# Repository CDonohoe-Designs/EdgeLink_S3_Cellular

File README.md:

# EdgeLink S3 Cellular

**ESP32-S3 Embedded Hardware Design | LTE-M / NB-IoT | GNSS | Battery Power Management | Four-Layer PCB | KiCad**

## Engineering overview

EdgeLink S3 Cellular is a four-layer embedded hardware platform combining an ESP32-S3 controller, SIM7080G cellular/GNSS modem, USB-C, battery power management and environmental/motion sensing.

I developed the Rev A schematic and PCB as an engineering portfolio project, demonstrating system architecture, wireless module integration, power-tree design, digital interfaces, multilayer layout and manufacturing documentation.

**Project status:** The schematic, PCB and manufacturing package are complete as design deliverables. Rev A is an **unbuilt design**; hardware bring-up and physical performance testing have not been completed.

## Engineering portfolio — start here

| Resource | Contents |
| --- | --- |
| **[Illustrated engineering portfolio (PDF)](docs/portfolio/EdgeLink_S3_Cellular/EdgeLink_S3_Cellular_Engineering_Portfolio.pdf)** | Six-page visual case study with genuine PCB renders, schematic extracts and manufacturing evidence |
| [Editable portfolio (Word)](docs/portfolio/EdgeLink_S3_Cellular/EdgeLink_S3_Cellular_Engineering_Portfolio.docx) | Editable report |
| [Portfolio images](docs/portfolio/EdgeLink_S3_Cellular/images/) | PCB top/bottom views, four copper layers, circuit extracts and CAD renders |
| [System architecture](docs/images/architecture-reva.svg) | Functional system diagram |
| [Complete schematic PDF](docs/schematics/EdgeLink_S3_Cellular_RevA_Schematic.pdf) | Hierarchical schematic |
| [Editable KiCad project](hardware/kicad/EdgeLink_S3_Cellular_RevA/EdgeLink_S3_Cellular.kicad_pro) | PCB, schematic and supporting libraries |
| [Manufacturing package](manufacturing/REV_A/) | Gerbers, BOM and component placement |

## Hardware architecture

| Subsystem | Implementation |
| --- | --- |
| Controller | ESP32-S3-MINI-1-N8 with Wi-Fi/Bluetooth LE and native USB |
| Cellular and positioning | SIMCom SIM7080G LTE-M / NB-IoT and GNSS |
| Charging and power path | TI BQ25185 |
| 3.3 V regulation | TI TPS63802 buck-boost |
| Battery monitoring | MAX17048 fuel gauge |
| Motion sensing | Bosch BMI323 six-axis IMU |
| Environmental sensing | SHT40 temperature/humidity and BMP384 pressure |
| External interfaces | USB-C, Nano-SIM, LTE/GNSS U.FL, battery and I²C |

USB-C provides input power and native USB data. The BQ25185 manages the battery and system supply, while the TPS63802 generates the main 3.3 V rail. The cellular modem is powered from the battery supply through its input filtering. The sensor subsystem uses I²C connections to the ESP32-S3.

## Schematic engineering

The hierarchical schematic separates power and USB, ESP32-S3 processing, cellular/GNSS and sensor interfaces. Key circuits include battery charging and regulation, modem power and UART connectivity, RF antenna interfaces, USB-C protection and digital sensor integration.

### ESP32-S3 controller core

The ESP32-S3-MINI-1-N8 schematic brings together the controller supply and decoupling, native USB connections, modem control signals, I²C interfaces, reset/boot circuitry and status LED.

### USB-C interface

## Four-layer PCB implementation

The Rev A PCB integrates power conversion, digital processing, wireless communications and sensors on a nominal 56 × 52 mm board. The layout uses four copper layers with local component decoupling and functional grouping of power, RF and digital circuitry.

Additional PCB views and genuine KiCad CAD renders are included in the [illustrated portfolio](docs/portfolio/EdgeLink_S3_Cellular/EdgeLink_S3_Cellular_Engineering_Portfolio.pdf).

## Manufacturing documentation

The Rev A package includes fabrication Gerbers, drill files, a supplier-oriented BOM with LCSC references and component placement data for JLCPCB-oriented assembly preparation.

The assembly BOM contains 46 component groups covering 89 fitted references, matched by the component placement list.

## Engineering capabilities demonstrated

- ESP32-S3 and wireless modem hardware integration
- USB-C and digital peripheral interfaces
- Battery charging, power-path and buck-boost architecture
- Four-layer PCB design and RF-aware placement/routing
- Hierarchical KiCad schematic capture and component libraries
- Supplier-oriented BOM, CPL and Gerber preparation
- Technical documentation and traceable engineering deliverables

## Repository guide

| Location | Contents |
| --- | --- |
| [Portfolio](docs/portfolio/EdgeLink_S3_Cellular/) | Illustrated PDF, Word report and supporting images |
| [KiCad source](hardware/kicad/EdgeLink_S3_Cellular_RevA/) | Editable design and local assets |
| [Architecture notes](docs/architecture/README.md) | Functional interfaces and power tree |
| [Manufacturing](manufacturing/REV_A/) | Fabrication and assembly files |
| [Verification records](docs/verification.md) | Detailed internal design-check documentation |
| [References](docs/references.md) | Manufacturer sources and CAD attribution |

**Tools:** KiCad 10, ESP32-S3 hardware design, wireless module integration, LCSC/JLCPCB-oriented manufacturing workflow and Git/GitHub.

No project-wide licence has been selected. Third-party assets retain their respective rights; see [references](docs/references.md).

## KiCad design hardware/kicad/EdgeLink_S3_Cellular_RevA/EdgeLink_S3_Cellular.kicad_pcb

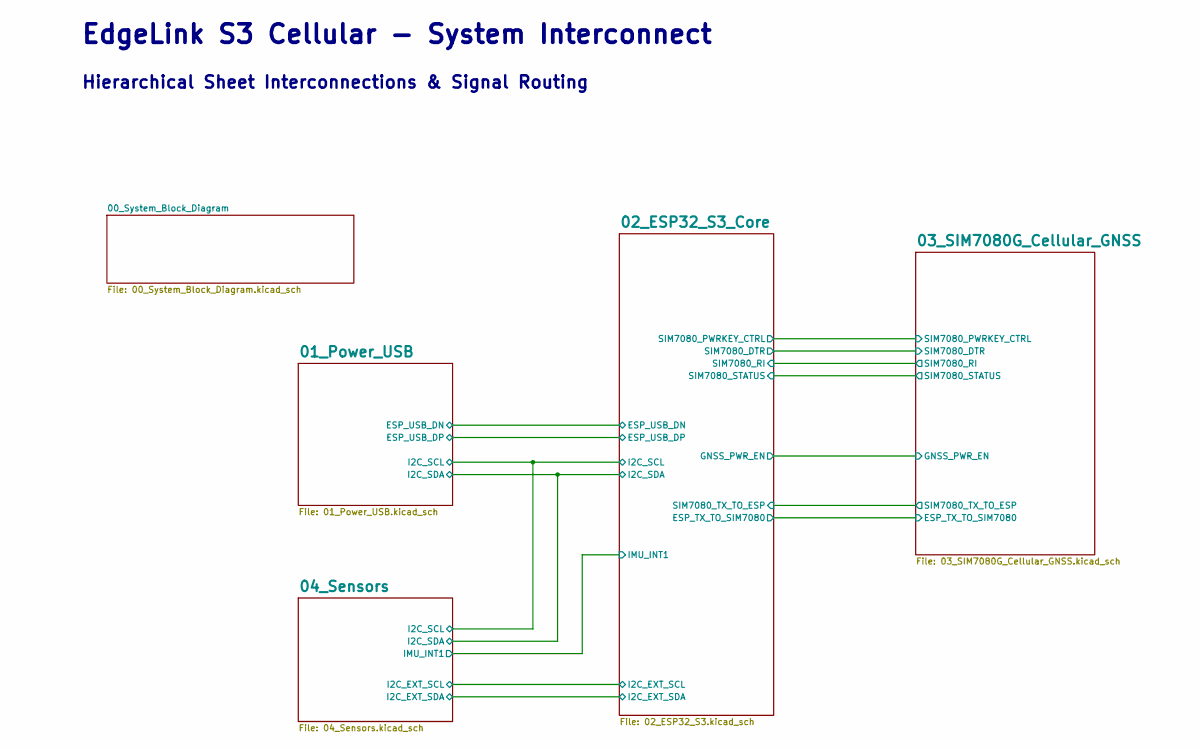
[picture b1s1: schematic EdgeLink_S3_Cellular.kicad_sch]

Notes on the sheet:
Hierarchical Sheet Interconnections & Signal Routing
EdgeLink S3 Cellular - System Interconnect

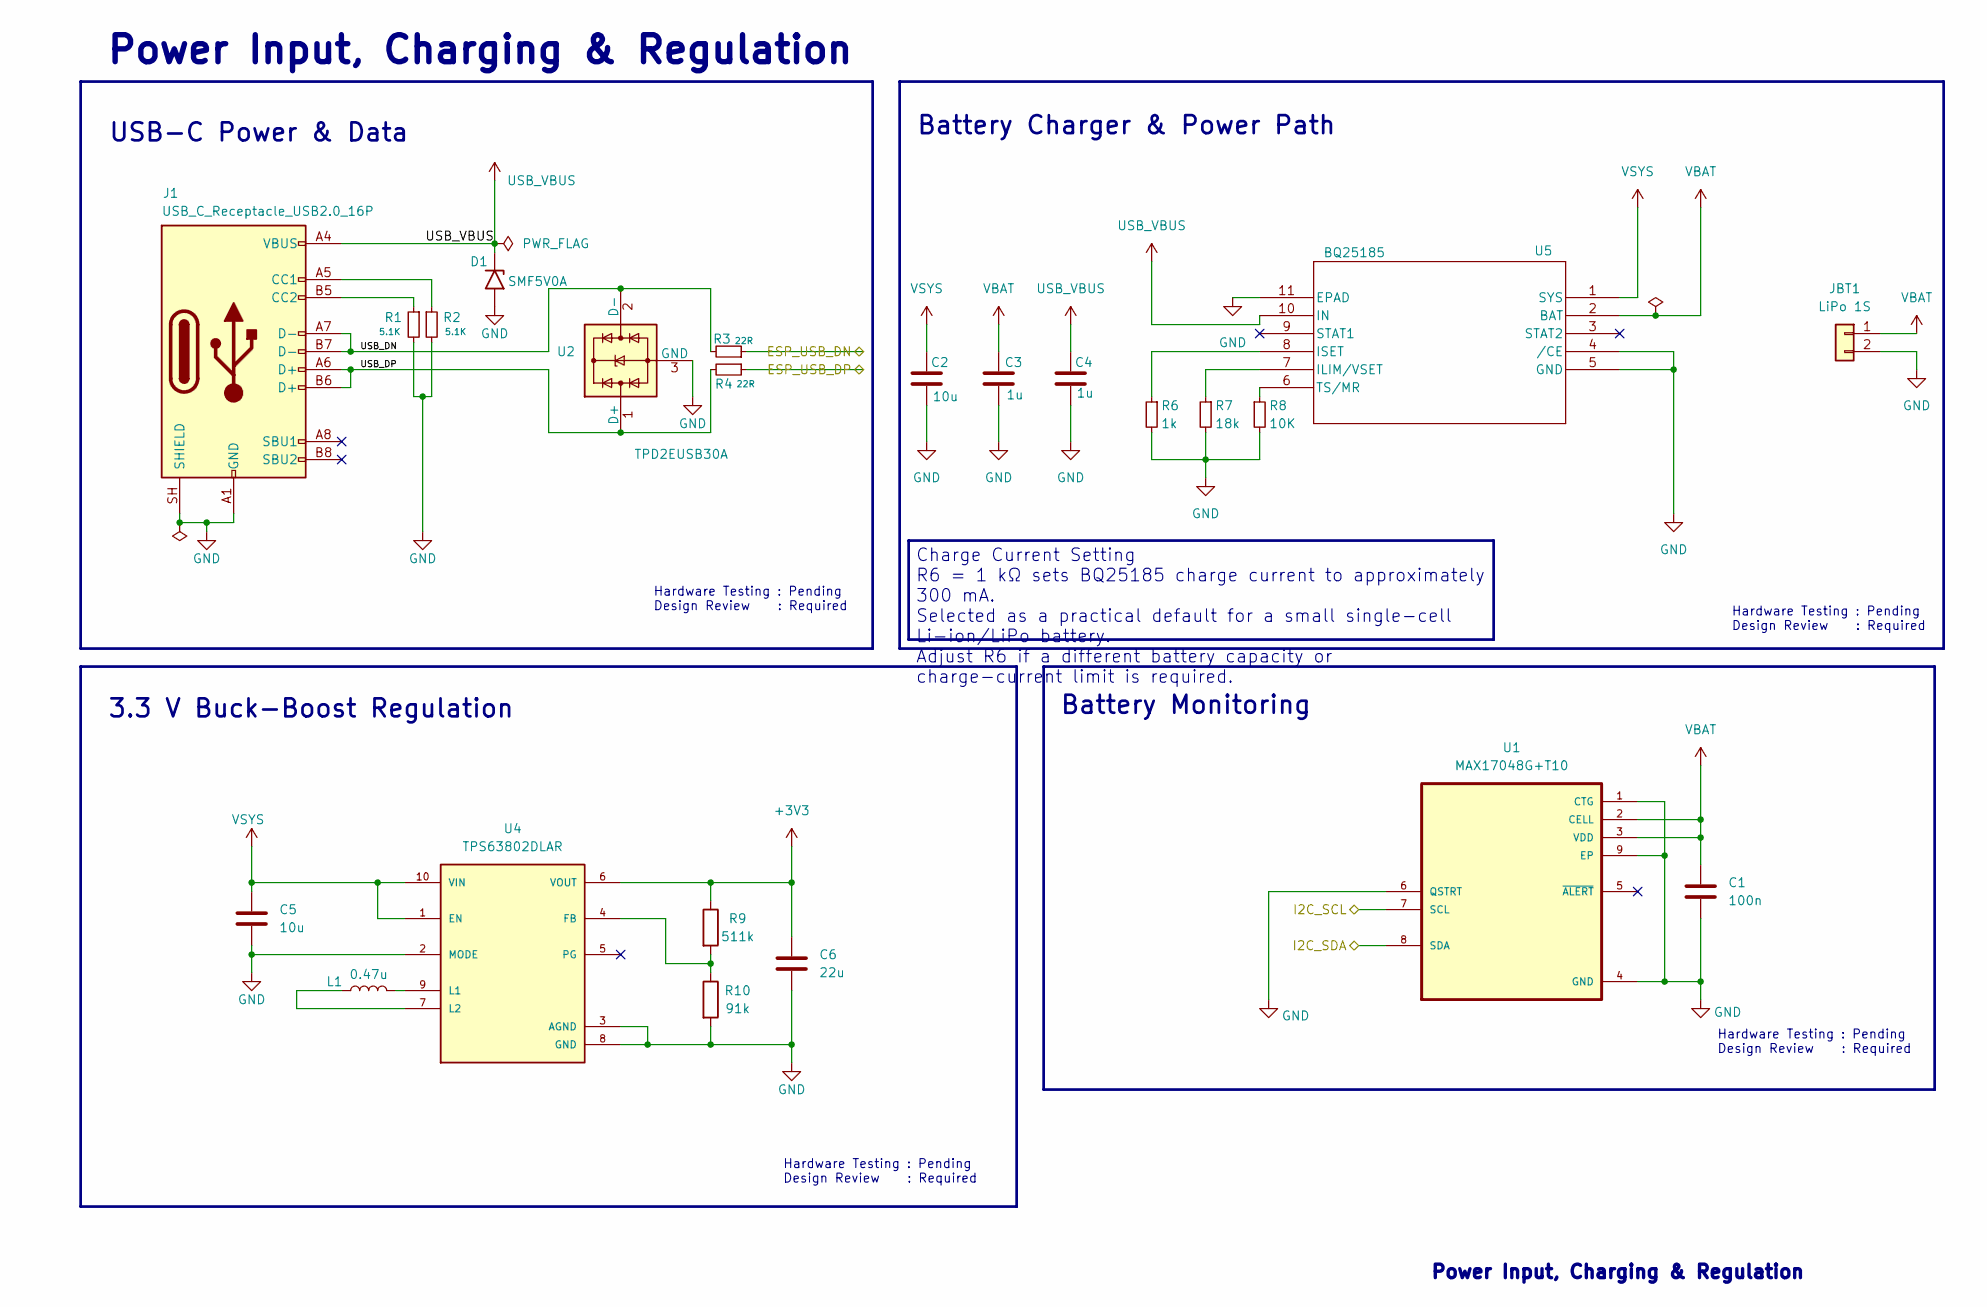
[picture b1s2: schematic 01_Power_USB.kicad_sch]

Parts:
C1: 100n; C_0402_1005Metric; MPN CL05B104KB54PNC; LCSC Part C307331
C2, C5: 10u; C_0603_1608Metric; MPN GRM188R61E106MA73D; LCSC Part C91606
C3, C4: 1u; C_0402_1005Metric; MPN CL05A105KA5NQNC; LCSC Part C52923
C6: 22u; C_0603_1608Metric; MPN CL10A226MO7JZNC; LCSC Part C2762594
D1: SMF5V0A; D_SMF; MPN SMF5V0A-E3-08; LCSC Part C1972946
J1: USB_C_Receptacle_USB2.0_16P; USB_C_Receptacle_GCT_USB4105-xx-A_16P_TopMnt_Horizontal; MPN USB4105-GF-A; digikey# 2073-USB4215-03-ACT-ND
JBT1: LiPo 1S; JST_PH_S2B-PH-SM4-TB_1x02-1MP_P2.00mm_Horizontal; MPN S2B-PH-SM4-TB(LF)(SN); LCSC Part C295747
L1: 0.47u; INDC2016X120N; MPN DFE201612E-R47M=P2; LCSC Part C668312
R1, R2: 5.1K; R_0402_1005Metric; MPN FRC0402F5101TS; digikey# YAG1696CT-ND
R3, R4: 22R; R_0402_1005Metric; MPN FRC0402F22R0TS; digikey# YAG1696CT-ND
R6: 1k; R_0402_1005Metric; MPN FRC0402F1001TS; LCSC Part C2906864
R7: 18k; R_0402_1005Metric; MPN FRC0402F1802TS; LCSC Part C2909327
R8: 10K; R_0402_1005Metric; MPN FRC0402F1002TS; LCSC Part C2906861
R9: 511k; R_0402_1005Metric; MPN FRC0402F5113TS; LCSC Part # C101109
R10: 91k; R_0402_1005Metric; MPN FRC0402F9102TS; LCSC Part # C25803
U1: MAX17048G+T10; TDFN-8-1EP_2x2mm_P0.5mm_EP0.8x1.2mm; MPN MAX17048G+T10; LCSC Part C2682616
U2: TPD2EUSB30A; Texas_DRT-3; MPN TPD2EUSB30ADRTR; LCSC Part C94934
U4: TPS63802DLAR; PARTREV B; LCSC Part # C2845237
U5: BQ25185; WSON10_DLH_TEX; MPN BQ25185DLHR; DigiKey 296-BQ25185DLHRCT-ND

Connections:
+3V3: C6.1, R9.1, U4.6 (VOUT); also elsewhere on the board
/01_Power_USB/ESP_USB_DN: R3.1; also elsewhere on the board
/01_Power_USB/ESP_USB_DP: R4.1; also elsewhere on the board
/01_Power_USB/USB_DN: J1.A7 (D-), J1.B7 (D-), R3.2, U2.2 (D-)
/01_Power_USB/USB_DP: J1.A6 (D+), J1.B6 (D+), R4.2, U2.1 (D+)
/04_Sensors/I2C_SCL: U1.7 (SCL); also elsewhere on the board
/04_Sensors/I2C_SDA: U1.8 (SDA); also elsewhere on the board
GND: C1.2, C2.2, C3.2, C4.2, C5.2, C6.2, D1.2 (A2), J1.A1 (GND), J1.A12 (GND), J1.B1 (GND), J1.B12 (GND), J1.SH (SHIELD), JBT1.2, R1.2, R2.2, R6.2, R7.2, R8.2, R10.2, U1.1 (CTG), U1.4 (GND), U1.6 (QSTRT), U1.9 (EP), U2.3 (GND), U4.2 (MODE), U4.3 (AGND), U4.8 (GND), U5.4 (/CE), U5.5 (GND), U5.11 (EPAD); also elsewhere on the board
unnamed: J1.A5 (CC1), R2.1
unnamed: J1.B5 (CC2), R1.1
unnamed: R9.2, R10.1, U4.4 (FB)
unnamed: L1.2, U4.9 (L1)
unnamed: L1.1, U4.7 (L2)
unnamed: R7.1, U5.7 (ILIM/VSET)
unnamed: R6.1, U5.8 (ISET)
unnamed: R8.1, U5.6 (TS/MR)
USB_VBUS: C4.1, D1.1 (A1), J1.A4 (VBUS), J1.A9 (VBUS), J1.B4 (VBUS), J1.B9 (VBUS), U5.10 (IN)
VBAT: C1.1, C3.1, JBT1.1, U1.2 (CELL), U1.3 (VDD), U5.2 (BAT); also elsewhere on the board
VSYS: C2.1, C5.1, U4.1 (EN), U4.10 (VIN), U5.1 (SYS)

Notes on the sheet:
3.3 V Buck-Boost Regulation
Hardware Testing : Pending Design Review : Required
Power Input, Charging & Regulation
USB-C Power & Data
Battery Monitoring
Battery Charger & Power Path
Charge Current Setting R6 = 1 kΩ sets BQ25185 charge current to approximately 300 mA. Selected as a practical default for a small single-cell Li-ion/LiPo battery. Adjust R6 if a different battery capacity or charge-current limit is required.

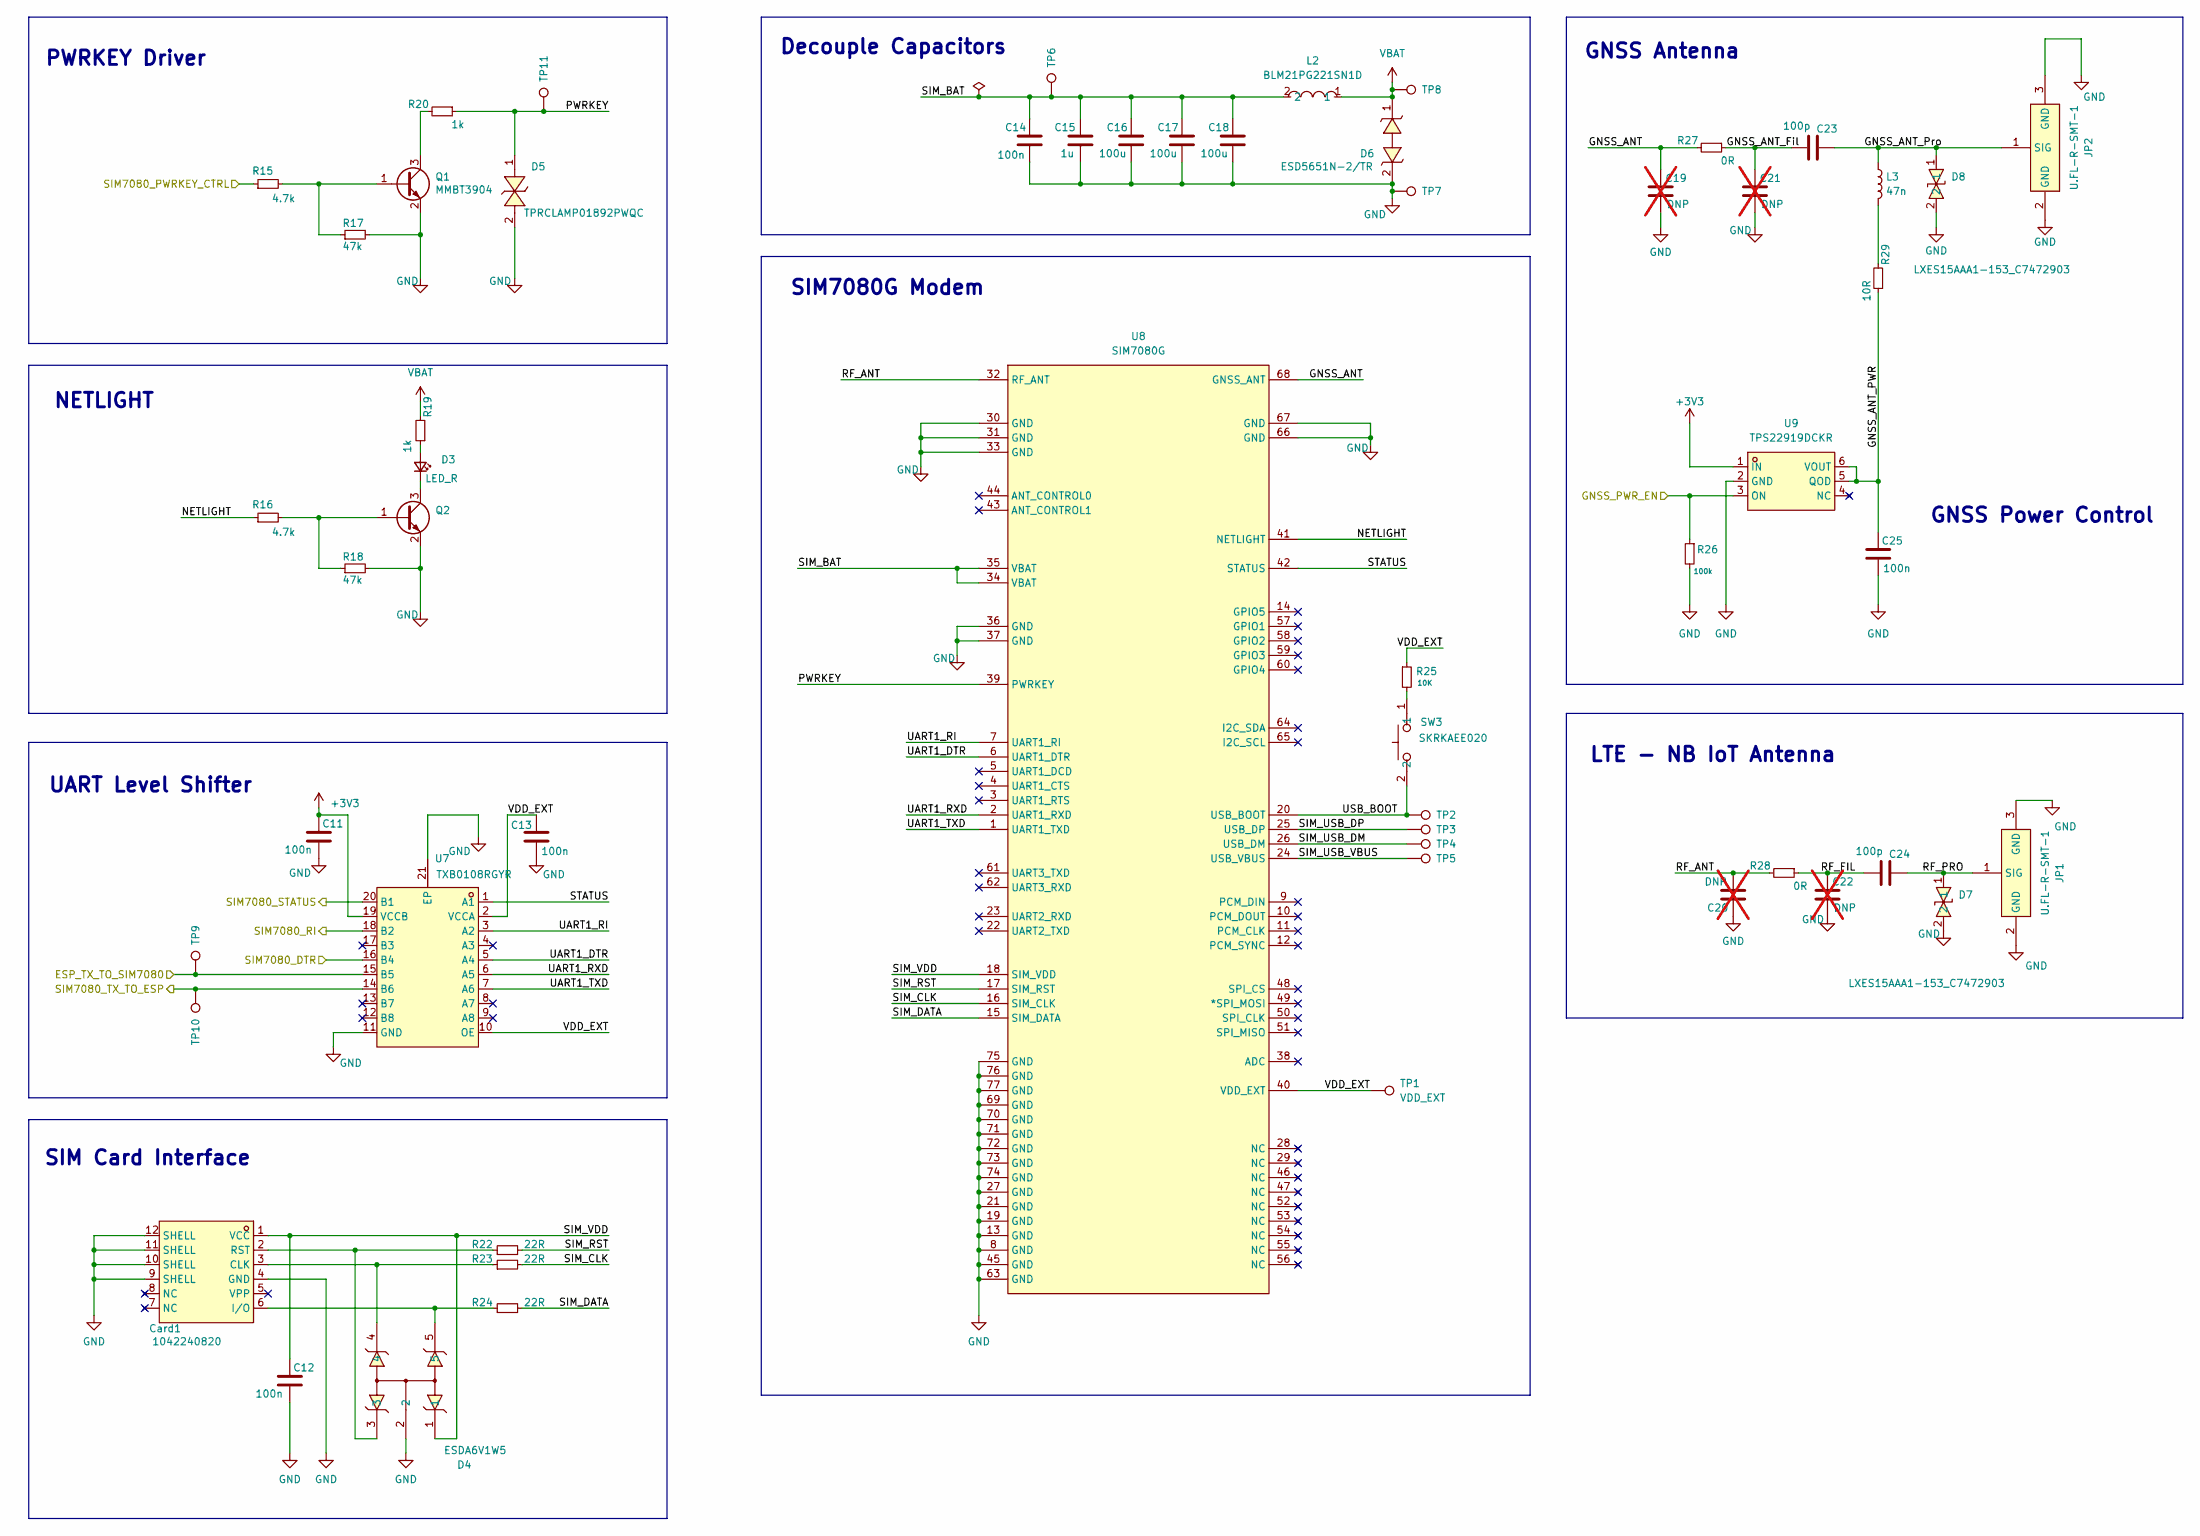
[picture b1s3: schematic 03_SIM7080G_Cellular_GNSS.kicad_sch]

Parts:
C11, C12, C13: 100n; C_0402_1005Metric; MPN CL05B104KB54PNC; LCSC Part C307331
C14, C25: 100n; C_0603_1608Metric; MPN CC0603KRX7R9BB104; LCSC Part C14663
C15: 1u; C_0402_1005Metric; MPN CL05A105KA5NQNC; LCSC Part C52923
C16, C17, C18: 100u; C_0805_2012Metric; MPN GRM21BR60J107ME15L; LCSC Part C141660
C19, C20, C21, C22: DNP; C_0402_1005Metric; not fitted
C23, C24: 100p; C_0402_1005Metric; MPN GCM1555C1H101JA16D; LCSC Part C126492
Card1: 1042240820; SIM-SMD_1042240820; MPN 1042240820; LCSC Part C585349
D3: LED_R; LED_0603_1608Metric; MPN LTST-C193KRKT-5A; digikey# 160-1830-1-ND
D4: ESDA6V1W5; SC-70-5_L2.1-W1.3-P0.65-LS2.1-BR; MPN ESDA6V1W5; LCSC Part C48677
D5: TPRCLAMP01892PWQC; DFN1006-2L-BI-1; MPN TPRCLAMP01892PWQC; LCSC Part C52098254
D6: ESD5651N-2/TR; DFN1006-2L-BI-1; MPN ESD5651N-2/TR; LCSC Part C239784
D7, D8: LXES15AAA1-153_C7472903; DFN1006-2L-BI; MPN LXES15AAA1-153; LCSC Part C7472903
JP1, JP2: U.FL-R-SMT-1; RF-SMD_FRF05002-JSS103M; MPN U.FL-R-SMT-1(80); LCSC Part C88374
L2: BLM21PG221SN1D; L0805; MPN BLM21PG221SN1D; LCSC Part C85840
L3: 47n; L_0402_1005Metric; MPN 0402DC-47NXJRW; LCSC Part C3221702
Q1, Q2: MMBT3904; SOT-23; MPN MMBT3904; LCSC Part C7420353
R15, R16: 4.7k; R_0402_1005Metric; MPN 0402WGF4701TCE; LCSC Part C25900
R17, R18: 47k; R_0402_1005Metric; MPN 0402WGF4702TCE; LCSC Part C25792
R19, R20: 1k; R_0402_1005Metric; MPN FRC0402F1001TS; LCSC Part C2906864
R22, R23, R24: 22R; R_0402_1005Metric; MPN FRC0402F22R0TS; LCSC Part C2929994
R25: 10K; R_0402_1005Metric; MPN FRC0402F1002TS; digikey# YAG1236CT-ND
R26: 100k; R_0402_1005Metric; MPN FRC0402F1003TS; digikey# YAG1696CT-ND
R27, R28: 0R; R_0402_1005Metric; MPN CQ02WGF0000TCE; LCSC Part C2770621
R29: 10R; R_0402_1005Metric; MPN FRC0402F10R0TS; LCSC Part C2906862
SW3: SKRKAEE020; SW-SMD_L3.9-W3.0-P4.45; MPN SKRKAEE020; LCSC Part C115357
TP1: VDD_EXT; TestPoint_Pad_D1.0mm
TP2: USB_BOOT; TestPoint_Pad_D1.0mm
TP3: SIM_USB_DP; TestPoint_Pad_D1.0mm
TP4: SIM_USB_DM; TestPoint_Pad_D1.0mm
TP5: SIM_USB_VBUS; TestPoint_Pad_D1.0mm
TP6: SIM_BAT; TestPoint_Pad_D1.0mm
TP7: GND; TestPoint_Pad_D1.0mm
TP8: VBAT; TestPoint_Pad_D1.0mm
TP9: ESP_TX_TO_SIM7080; TestPoint_Pad_D1.0mm
TP10: SIM7080_TX_TO_ESP; TestPoint_Pad_D1.0mm
TP11: PWRKEY; TestPoint_Pad_D1.0mm
U7: TXB0108RGYR; VQFN-20_L4.5-W3.5-P0.50-BL-EP; MPN TXB0108RGYR; LCSC Part C194701
U8: SIM7080G; LCC-SMD_SIM7080G; MPN SIM7080G; LCSC Part C2943992
U9: TPS22919DCKR; SC-70-6_L2.2-W1.3-P0.65-LS2.1-BR; MPN TPS22919DCKR; LCSC Part C2149796

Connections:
+3V3: C11.1, U7.19 (VCCB), U9.1 (IN); also elsewhere on the board
/02_ESP32_S3_Core/ESP_TX_TO_SIM7080: TP9.1 (1_1), U7.15 (B5); also elsewhere on the board
/02_ESP32_S3_Core/GNSS_PWR_EN: R26.1, U9.3 (ON); also elsewhere on the board
/02_ESP32_S3_Core/SIM7080_DTR: U7.16 (B4); also elsewhere on the board
/02_ESP32_S3_Core/SIM7080_PWRKEY_CTRL: R15.1; also elsewhere on the board
/02_ESP32_S3_Core/SIM7080_RI: U7.18 (B2); also elsewhere on the board
/02_ESP32_S3_Core/SIM7080_STATUS: U7.20 (B1); also elsewhere on the board
/02_ESP32_S3_Core/SIM7080_TX_TO_ESP: TP10.1 (1_1), U7.14 (B6); also elsewhere on the board
/03_SIM7080G_Cellular_GNSS/GNSS_ANT: C19.1, R27.2, U8.68 (GNSS_ANT)
/03_SIM7080G_Cellular_GNSS/GNSS_ANT_Fil: C21.1, C23.2, R27.1
/03_SIM7080G_Cellular_GNSS/GNSS_ANT_PWR: C25.1, R29.1, U9.5 (QOD), U9.6 (VOUT)
/03_SIM7080G_Cellular_GNSS/GNSS_ANT_Pro: C23.1, D8.1, JP2.1 (SIG), L3.1
/03_SIM7080G_Cellular_GNSS/NETLIGHT: R16.1, U8.41 (NETLIGHT)
/03_SIM7080G_Cellular_GNSS/PWRKEY: D5.1, R20.1, TP11.1 (1_1), U8.39 (PWRKEY)
/03_SIM7080G_Cellular_GNSS/RF_ANT: C20.2, R28.2, U8.32 (RF_ANT)
/03_SIM7080G_Cellular_GNSS/RF_FIL: C22.1, C24.2, R28.1
/03_SIM7080G_Cellular_GNSS/RF_PRO: C24.1, D7.1, JP1.1 (SIG)
/03_SIM7080G_Cellular_GNSS/SIM_BAT: C14.1, C15.1, C16.1, C17.1, C18.1, L2.2, TP6.1 (1_1), U8.34 (VBAT), U8.35 (VBAT)
/03_SIM7080G_Cellular_GNSS/SIM_CLK: R23.2, U8.16 (SIM_CLK)
/03_SIM7080G_Cellular_GNSS/SIM_DATA: R24.2, U8.15 (SIM_DATA)
/03_SIM7080G_Cellular_GNSS/SIM_RST: R22.2, U8.17 (SIM_RST)
/03_SIM7080G_Cellular_GNSS/SIM_USB_DM: TP4.1 (1_1), U8.26 (USB_DM)
/03_SIM7080G_Cellular_GNSS/SIM_USB_DP: TP3.1 (1_1), U8.25 (USB_DP)
/03_SIM7080G_Cellular_GNSS/SIM_USB_VBUS: TP5.1 (1_1), U8.24 (USB_VBUS)
/03_SIM7080G_Cellular_GNSS/SIM_VDD: C12.1, Card1.1 (VCC), D4.1, U8.18 (SIM_VDD)
/03_SIM7080G_Cellular_GNSS/STATUS: U7.1 (A1), U8.42 (STATUS)
/03_SIM7080G_Cellular_GNSS/UART1_DTR: U7.5 (A4), U8.6 (UART1_DTR)
/03_SIM7080G_Cellular_GNSS/UART1_RI: U7.3 (A2), U8.7 (UART1_RI)
/03_SIM7080G_Cellular_GNSS/UART1_RXD: U7.6 (A5), U8.2 (UART1_RXD)
/03_SIM7080G_Cellular_GNSS/UART1_TXD: U7.7 (A6), U8.1 (UART1_TXD)
/03_SIM7080G_Cellular_GNSS/USB_BOOT: SW3.2, TP2.1 (1_1), U8.20 (USB_BOOT)
/03_SIM7080G_Cellular_GNSS/VDD_EXT: C13.1, R25.1, TP1.1 (1_1), U7.2 (VCCA), U7.10 (OE), U8.40 (VDD_EXT)
GND: C11.2, C12.2, C13.2, C14.2, C15.2, C16.2, C17.2, C18.2, C19.2, C20.1, C21.2, C22.2, C25.2, Card1.4 (GND), Card1.9 (SHELL), Card1.10 (SHELL), Card1.11 (SHELL), Card1.12 (SHELL), D4.2, D5.2, D6.2, D7.2, D8.2, JP1.2 (GND), JP1.3 (GND), JP2.2 (GND), JP2.3 (GND), Q1.2 (E), Q2.2 (E), R17.2, R18.2, R26.2, TP7.1 (1_1), U7.11 (GND), U7.21 (EP), U8.8 (GND), U8.13 (GND), U8.19 (GND), U8.21 (GND), U8.27 (GND), U8.30 (GND), U8.31 (GND), U8.33 (GND), U8.36 (GND), U8.37 (GND), U8.45 (GND), U8.63 (GND), U8.66 (GND), U8.67 (GND), U8.69 (GND), U8.70 (GND), U8.71 (GND), U8.72 (GND), U8.73 (GND), U8.74 (GND), U8.75 (GND), U8.76 (GND), U8.77 (GND), U9.2 (GND); also elsewhere on the board
unnamed: Card1.3 (CLK), D4.4, R23.1
unnamed: Card1.6 (I/O), D4.5, R24.1
unnamed: Card1.2 (RST), D4.3, R22.1
unnamed: D3.2 (A), R19.1
unnamed: D3.1 (K), Q2.3 (C)
unnamed: L3.2, R29.2
unnamed: Q1.1 (B), R15.2, R17.1
unnamed: Q1.3 (C), R20.2
unnamed: Q2.1 (B), R16.2, R18.1
unnamed: R25.2, SW3.1
VBAT: D6.1, L2.1, R19.2, TP8.1 (1_1); also elsewhere on the board

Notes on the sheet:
UART Level Shifter
Decouple Capacitors
PWRKEY Driver
SIM7080G Modem
GNSS Antenna
LTE - NB IoT Antenna
GNSS Power Control
NETLIGHT
SIM Card Interface

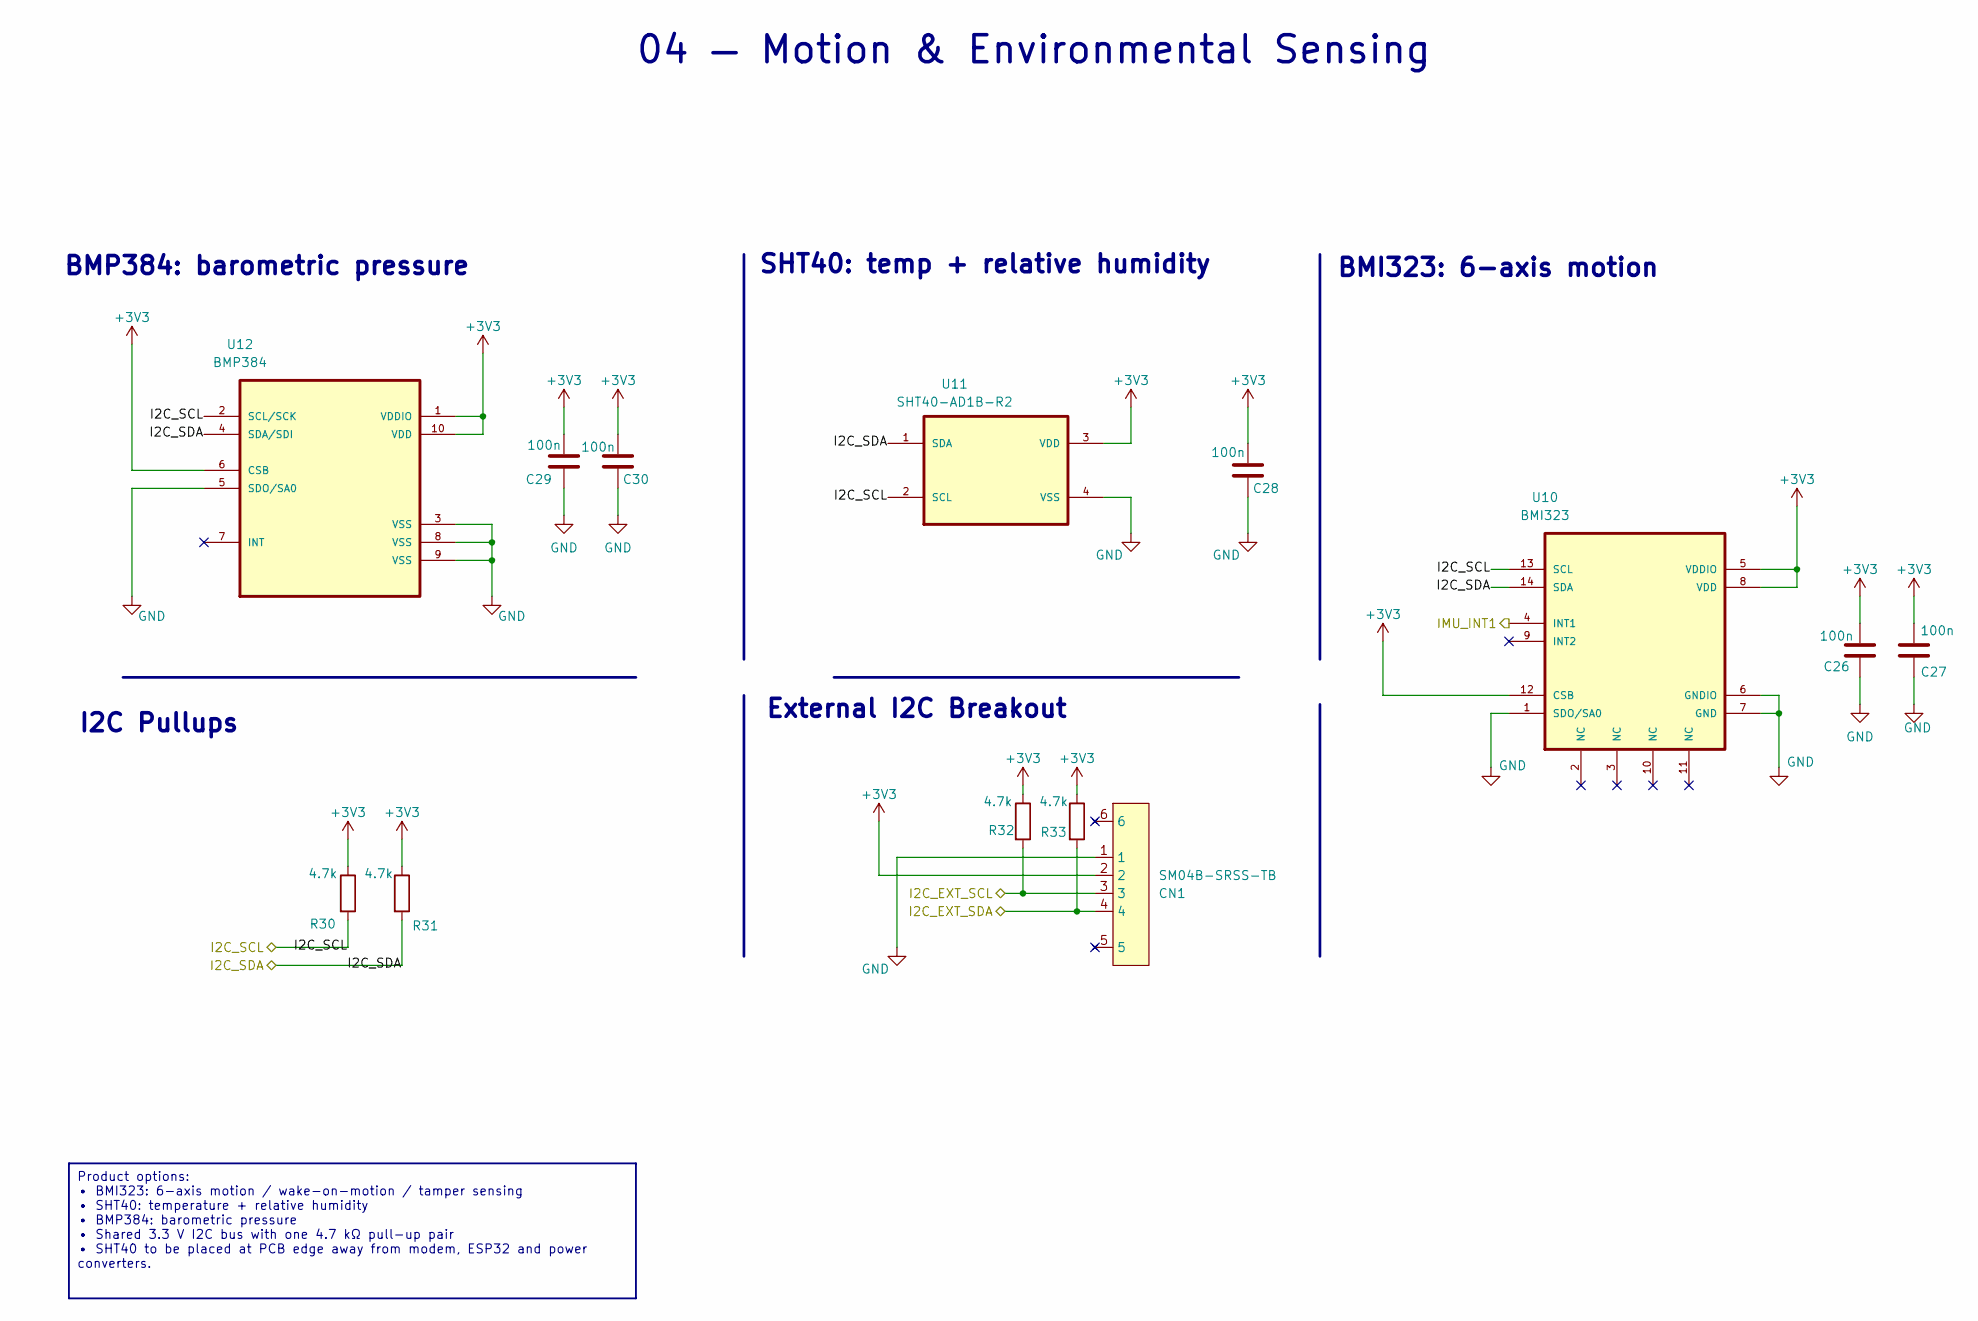
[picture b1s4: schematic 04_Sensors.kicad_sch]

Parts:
C26, C27, C28, C29, C30: 100n; C_0402_1005Metric; MPN CL05B104KB54PNC; LCSC Part C307331
CN1: SM04B-SRSS-TB; CONN-SMD_4P-P1.00_SM04B-SRSS-TB-LF-SN; MPN SM04B-SRSS-TB(LF)(SN); LCSC Part C160404
R30, R31, R32, R33: 4.7k; R_0402_1005Metric; MPN 0402WGF4701TCE; LCSC Part C25900
U10: BMI323; Bosch_LGA-14_3x2.5mm_P0.5mm; MPN BMI323; LCSC Part # C5368700
U11: SHT40-AD1B-R2; SHT4x_DFN4_1.5x1.5mm; MPN SHT40-AD1B-R2; LCSC Part # C2909890
U12: BMP384; BMP390_LGA10_2x2mm; MPN BMP384; LCSC Part # C5577555

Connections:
+3V3: C26.1, C27.1, C28.1, C29.1, C30.1, CN1.2, R30.1, R31.1, R32.1, R33.1, U10.5 (VDDIO), U10.8 (VDD), U10.12 (CSB), U11.3 (VDD), U12.1 (VDDIO), U12.6 (CSB), U12.10 (VDD); also elsewhere on the board
/02_ESP32_S3_Core/I2C_EXT_SCL: CN1.3, R32.2; also elsewhere on the board
/02_ESP32_S3_Core/I2C_EXT_SDA: CN1.4, R33.2; also elsewhere on the board
/02_ESP32_S3_Core/IMU_INT1: U10.4 (INT1); also elsewhere on the board
/04_Sensors/I2C_SCL: R30.2, U10.13 (SCL), U11.2 (SCL), U12.2 (SCL/SCK); also elsewhere on the board
/04_Sensors/I2C_SDA: R31.2, U10.14 (SDA), U11.1 (SDA), U12.4 (SDA/SDI); also elsewhere on the board
GND: C26.2, C27.2, C28.2, C29.2, C30.2, CN1.1, U10.1 (SDO/SA0), U10.6 (GNDIO), U10.7 (GND), U11.4 (VSS), U12.3 (VSS), U12.5 (SDO/SA0), U12.8 (VSS), U12.9 (VSS); also elsewhere on the board

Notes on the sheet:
SHT40: temp + relative humidity
BMP384: barometric pressure
04 — Motion & Environmental Sensing
BMI323: 6-axis motion
External I2C Breakout
I2C Pullups
Product options: • BMI323: 6-axis motion / wake-on-motion / tamper sensing • SHT40: temperature + relative humidity • BMP384: barometric pressure • Shared 3.3 V I2C bus with one 4.7 kΩ pull-up pair • SHT40 to be placed at PCB edge away from modem, ESP32 and power converters.

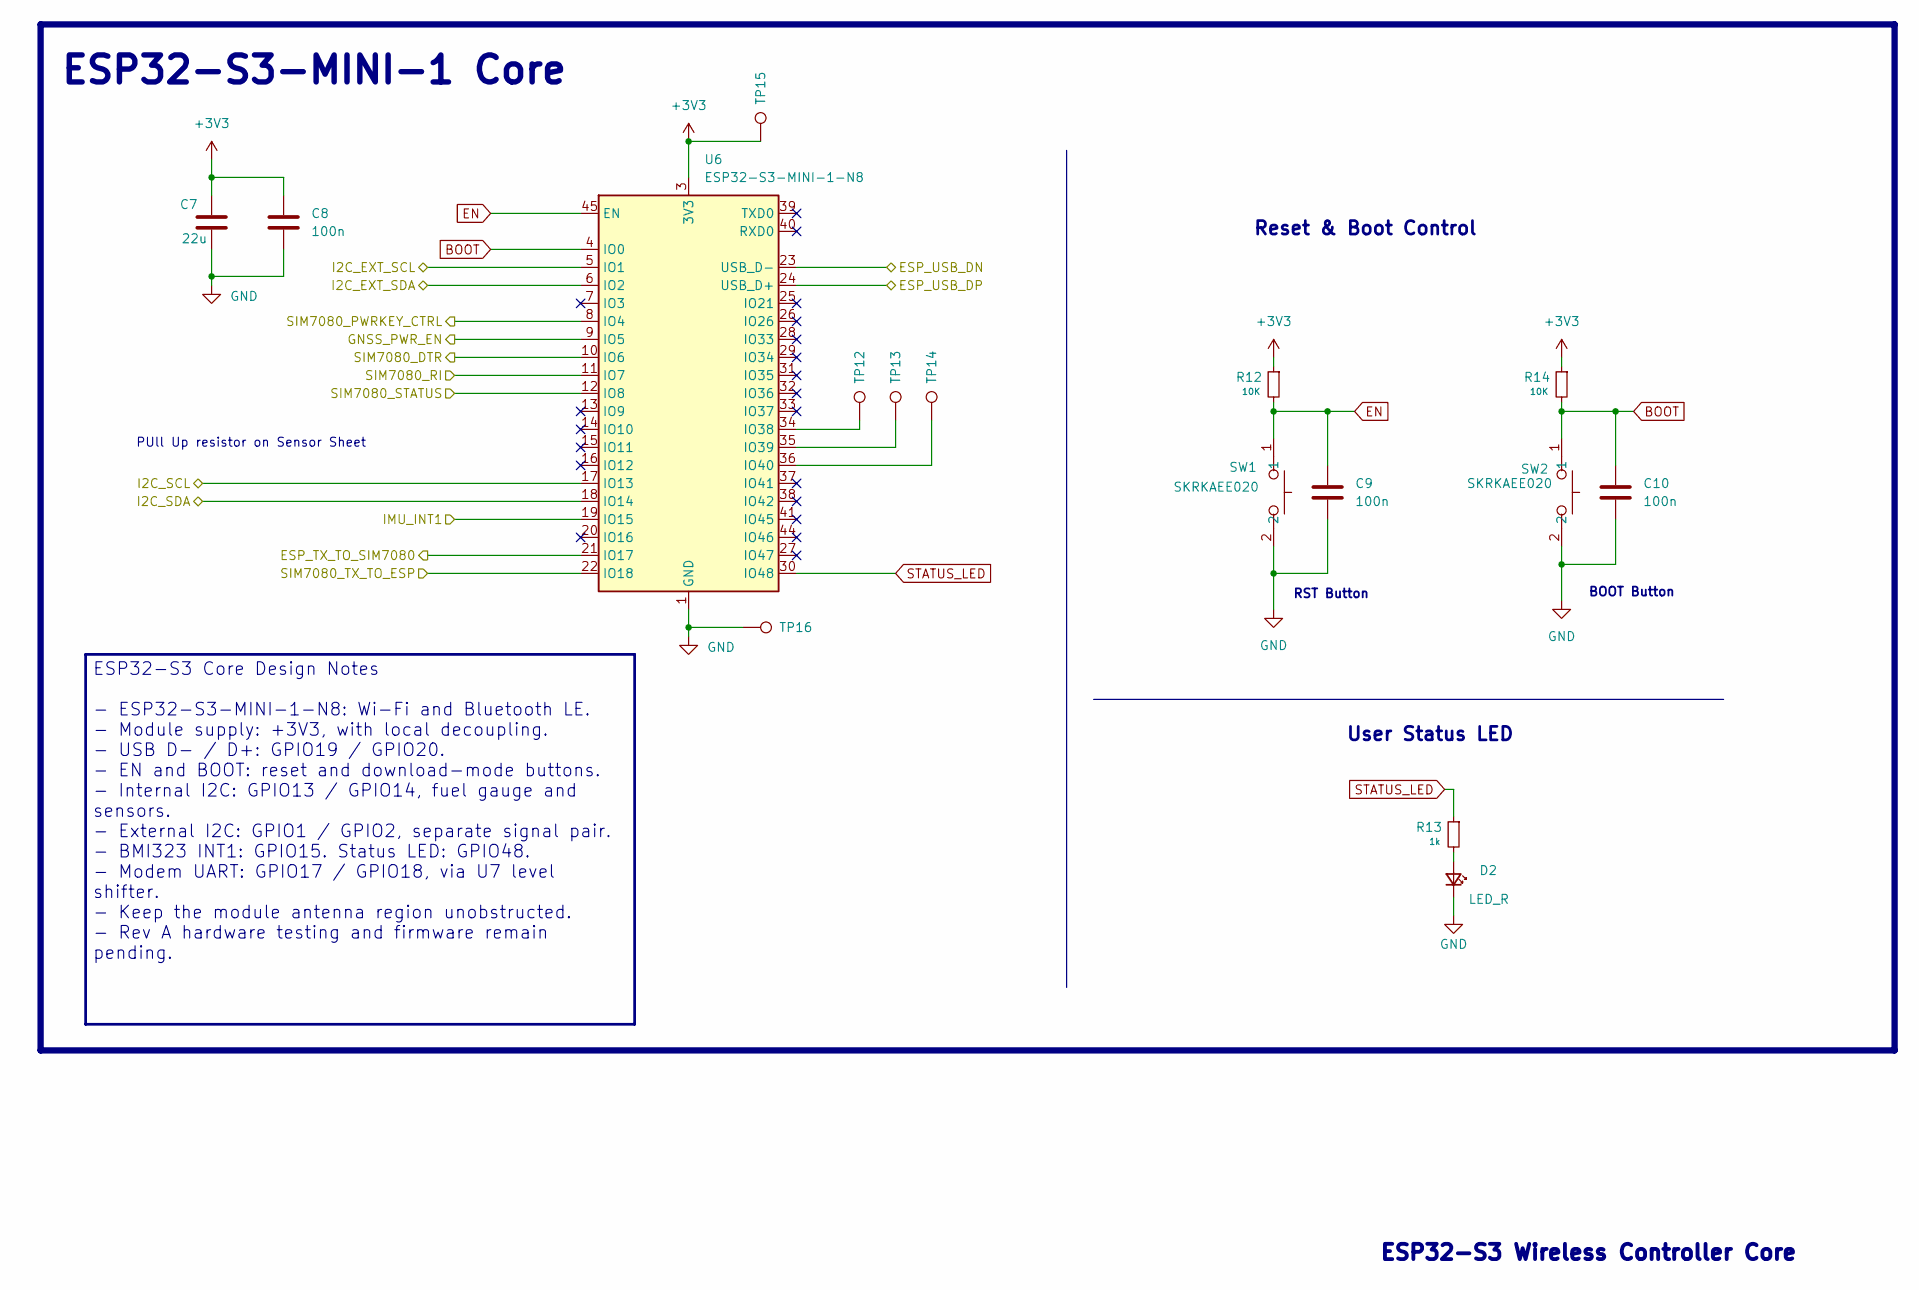
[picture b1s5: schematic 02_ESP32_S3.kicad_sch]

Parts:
C7: 22u; C_0603_1608Metric; MPN CL10A226MO7JZNC; LCSC Part C2762594
C8, C9, C10: 100n; C_0402_1005Metric; MPN CL05B104KB54PNC; LCSC Part C307331
D2: LED_R; LED_0603_1608Metric; MPN LTST-C193KRKT-5A; digikey# 160-1830-1-ND
R12, R14: 10K; R_0402_1005Metric; MPN FRC0402F1002TS; digikey# YAG1236CT-ND
R13: 1k; R_0402_1005Metric; MPN FRC0402F1001TS; digikey# YAG1696CT-ND
SW1, SW2: SKRKAEE020; SW-SMD_L3.9-W3.0-P4.45; MPN SKRKAEE020; LCSC Part C115357
TP12, TP13, TP14, TP15, TP16: PWRKEY; TestPoint_Pad_D1.0mm
U6: ESP32-S3-MINI-1-N8; ESP32-S2-MINI-1; MPN ESP32-S3-MINI-1-N8; LCSC Part C2913206

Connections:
+3V3: C7.1, C8.1, R12.1, R14.1, TP15.1 (1_1), U6.3 (3V3); also elsewhere on the board
/01_Power_USB/ESP_USB_DN: U6.23 (USB_D-); also elsewhere on the board
/01_Power_USB/ESP_USB_DP: U6.24 (USB_D+); also elsewhere on the board
/02_ESP32_S3_Core/ESP_TX_TO_SIM7080: U6.21 (IO17); also elsewhere on the board
/02_ESP32_S3_Core/GNSS_PWR_EN: U6.9 (IO5); also elsewhere on the board
/02_ESP32_S3_Core/I2C_EXT_SCL: U6.5 (IO1); also elsewhere on the board
/02_ESP32_S3_Core/I2C_EXT_SDA: U6.6 (IO2); also elsewhere on the board
/02_ESP32_S3_Core/IMU_INT1: U6.19 (IO15); also elsewhere on the board
/02_ESP32_S3_Core/SIM7080_DTR: U6.10 (IO6); also elsewhere on the board
/02_ESP32_S3_Core/SIM7080_PWRKEY_CTRL: U6.8 (IO4); also elsewhere on the board
/02_ESP32_S3_Core/SIM7080_RI: U6.11 (IO7); also elsewhere on the board
/02_ESP32_S3_Core/SIM7080_STATUS: U6.12 (IO8); also elsewhere on the board
/02_ESP32_S3_Core/SIM7080_TX_TO_ESP: U6.22 (IO18); also elsewhere on the board
/04_Sensors/I2C_SCL: U6.17 (IO13); also elsewhere on the board
/04_Sensors/I2C_SDA: U6.18 (IO14); also elsewhere on the board
BOOT: C10.1, R14.2, SW2.1, U6.4 (IO0)
EN: C9.1, R12.2, SW1.1, U6.45 (EN)
GND: C7.2, C8.2, C9.2, C10.2, D2.1 (K), SW1.2, SW2.2, TP16.1 (1_1), U6.1 (GND), U6.2 (GND), U6.42 (GND), U6.43 (GND), U6.46 (GND), U6.47 (GND), U6.48 (GND), U6.49 (GND), U6.50 (GND), U6.51 (GND), U6.52 (GND), U6.53 (GND), U6.54 (GND), U6.55 (GND), U6.56 (GND), U6.57 (GND), U6.58 (GND), U6.59 (GND), U6.60 (GND), U6.61 (GND), U6.62 (GND), U6.63 (GND), U6.64 (GND), U6.65 (GND); also elsewhere on the board
unnamed: D2.2 (A), R13.2
unnamed: TP12.1 (1_1), U6.34 (IO38)
unnamed: TP13.1 (1_1), U6.35 (IO39)
unnamed: TP14.1 (1_1), U6.36 (IO40)
STATUS_LED: R13.1, U6.30 (IO48)

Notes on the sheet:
PUll Up resistor on Sensor Sheet
BOOT Button
Reset & Boot Control
User Status LED
RST Button
ESP32-S3 Wireless Controller Core
ESP32-S3-MINI-1 Core
ESP32-S3 Core Design Notes - ESP32-S3-MINI-1-N8: Wi-Fi and Bluetooth LE. - Module supply: +3V3, with local decoupling. - USB D- / D+: GPIO19 / GPIO20. - EN and BOOT: reset and download-mode buttons. - Internal I2C: GPIO13 / GPIO14, fuel gauge and sensors. - External I2C: GPIO1 / GPIO2, separate sig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
